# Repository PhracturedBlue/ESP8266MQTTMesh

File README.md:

# ESP8266MQTTMesh
Self-assembling mesh network built around the MQTT protocol for the ESP8266 with OTA support

## NOTE 2020-04
I no longer have resources to work on this, and there are several issues that need to be addressed.  If you have the desire and skill to contribute to this project, please comment on https://github.com/PhracturedBlue/ESP8266MQTTMesh/issues/75 and I will consider your offer of help

## Overview
This code provides a library that can build a mesh network between ESP8266 devices that will allow all nodes to communicate
with an MQTT broker.  At least one node must be able to see a wiFi router, and there must be a host on the WiFi network running
the MQTT broker.
Nodes cannot (generally) communicate between themselves, but instead forward all messages through the broker.
Each node will expose a hidden AP which can be connected to from any other node on the network.  Note:  hiding the AP does not provide
any additional security, but does minimize the clutter of other WiFi clients in the area.

Additionally the library provides an OTA mechanism using the MQTT pathway which can update any/all nodes on the mesh.

This code was developed primarily for the Sonoff line of relays, but should work with any ESP8266 board with sufficient flash memory

Further information about the mesh topology can be found [here](docs/MeshTopology.md)

### Note for version >= 1.0
As of version 1.0 the nodes no longer need to connect to the broker once before use.  Nodes can self-identify other nodes automatically
and do not store any needed state on the broker.  Nodes use the MAC address to identify other nodes, and the ESP8266MQTTMesh code
will change the node's MAC address to match the required pattern.  The MAC addresses are based on both the node's chipID as well as the mesh password, ensuring that each node will have a unique MAC address as well as that multiple meshes can run in the same area independently.

Also, he ESP8266MQTTMesh code no longer uses the SPIFFS file-system.  If you need it, you'll need to initialize it yourself.  If
the mesh is configured to use SSL between nodes, the SSL certs need to be provided during initalization

## OTA
While all nodes must run the same version of the ESP8622MQTTMesh library, each node may run a unique firmware with independent purposes.
The main purpose behind this library was to provide a backbone on which several home-automation sensors could be built.  As such
each node may need different code to achieve its purpose.  Because firmwares are large, and memory is limited on the ESP8266 platform,
there is only a single memory area to hold the incoming firmware.  To ensure that a given firmware is only consumed by the proper nodes,
The firmware defines a unique identifier that distinguishes itself from other code.  A given firmware is broadcast from the MQTT
broker to all nodes, but only nodes with a matching ID will update.

## Using the Library
### Prerequisites
This library has been converted to use Asynchronous communication for imroved reliability.  It requires the following libraries to be installed
* AsyncMqttClient
* ESPAsyncTCP
* Arduino ESP8266 Core version 2.4

PlatformIO is strongly recommended, and installation instructions can be found [here](http://docs.platformio.org/en/latest/platforms/espressif8266.html)).

**NOTE:** Enabling SSL will add ~70kB to the firmware size, and may make it impossible to use OTA updates depending on firmware and flash size.

If OTA support is desired, the esp8266 module must have at least 1M of Flash (configured as >=784k ROM).  The OTA image is stored
between the end of the firmware image and the beginning of the filesystem (i.e. not in the filesystem itself) or the end of flash if
no filesystem is present.  Thus, ithe maximum firmware size is ~ 1/2 the available Flash.

### Library initialization
The ESP8266MQTTMesh only requires 2 parameters to initialize, but there are many additional optional parameters:
```
ESP8266MQTTMesh mesh = ESP8266MQTTMesh::Builder(networks, mqtt_server, mqtt_port).build();
```
- `wifi_conn networks[]` *Required*: A list of SSIDs/BSSIDs/passwords to search for to connect to the wireless network.  The list should be terminated with a NULL element.
- `const char *mqtt_server` *Required*: Host which runs the MQTT broker
- `int mqtt_port` *Optional*: Port which the MQTT broker is running on.  Defaults to 1883 if MQTT SSL is not enabled.  Defaults to 8883 is MQTT SSL is enabled

Additional Parameters can be enabled via the *Builder* for example:
```
ESP8266MQTTMesh mesh = ESP8266MQTTMesh::Builder(networks, mqtt_server, mqtt_port)
                       .setVersion(firmware_ver, firmware_id)
                       .setMeshPassword(password)
                       .build();
```
These additional parameters are specified before calling build(), and as few or as many can be used as neeeded.

```
setVersion(firmware_ver, firmware_id)
```
- `const char *firmware_ver`: This is a string that idenitfies the firmware.  It can be whatever you like.  It will be broadcast to the MQTT broker on successful connection
- `int firmware_id`:  This identifies a specific node codebase.  Each unique firmware should have its own id, and it should not be changed between revisions of the code

```
setMqttAuth(username, password)
```
- `const char *username`: The username used to login to the MQTT broker
- `const char *password`: The password used to login to the MQTT broker

```
setMeshPassword(password)
```
- `const char *password`: The password to use when a node connects to another node on the mesh.  Default: `ESP8266MQTTMesh`

```
setMeshSSID(ssid)
```
- `const char *ssid`: The SSID used by mesh nodes.  All nodes will use the same SSID, though this isn't noticeable due to nodes using hidden networks.  Default: `esp8266_mqtt_mesh

```
setMeshPort(port)
```
- `int port`: Port for mesh nodes to listen on for message parsing. Default: `1884`

```
setTopic(in_topic, out_topic)
```
- `const char *in_topic`: MQTT topic prefix for messages sent to the node.  Default: `esp8266-in/`
- `const char *out_topic`: MQTT topic prefix for messages from the node. Default: `esp8266-out/`

If SSL support is enabled, the following optional parameters are available:
```
setMqttSSL(enable, fingerprint)
```
- `bool enable`: Enable MQTT SSL support.  Default: `false`
- `const uint8_t *fingerprint`: Fingerprint to verify MQTT certificate (prevent man-in-the-middle attacks)

```
setMeshSSL(cert, cert_len, key, key_len, fingerprint)
```
- `const uint8_t *cert`: Certificate
- `uint32_t cert_len`: Certificate length
- `const uint8_t *key`: Certificate key
- `uint32_t key_len`: Certificate key length
- `uint8_t *fingerprint`: Certificate fingerprint (SHA1 of certificate)

### Interacting with the mesh
Besides the constructor, the code must call the `begin()` method during setup.

If messages need to be received by the node, execute the `callback()` function during setup with a function pointer
(prototype: `void callback(const char *topic, const char *payload)`)

To send messages to the MQTT broker, use one of the publish methods:
```
publish(topic, payload, msgCmd)
publish_node(topic, payload, msgCmd)
```
The `publish` function sends messages with the `out_topic` prefix, and will not be relayed to any nodes.  The `publish_nodes`
function will send messages with the `in_topic` prefix and will be relayed back to all nodes

- `const char *topic`: the message topic (will be appended to the topic-prefix)
- `const char *payload`: The message to send (must be less than 1152 bytes in length)
- `enum MSG_TYPE msgCmd`: The MQTT Retail/QoS parameters (optional).  Must be one of: `MSG_TYPE_NONE`,
  `MSG_TYPE_QOS_0`, `MSG_TYPE_QOS_1`, `MSG_TYPE_QOS_2`, `MSG_TYPE_RETAIN_QOS_0`, MSG_TYPE_RETAIN_QOS_1`,
  `MSG_TYPE_RETAIN_QOS_2`.  Default: `MSG_TYPE_NONE`

### SSL support
SSL support is enabled by defining `ASYNC_TCP_SSL_ENABLED=1`.  This must be done globally during build.

Once enabled, SSL can be optionally enabled between the node and the MQTT broker or between mesh nodes (or both).

#### Using SSL with the MQTT Broker
**WARNING:** Make sure you do not use SHA512 certificate signatures on your MQTT broker.  They are not suppoorted by ESP8266 properly
Using an optional fingerprint ensures that the MQTT Broker is the one you expect.  Specifying a fingerprint is useful to prevent man-in-the-middle attacks.
The fingerprint can be generated by running:
```
utils/get_mqtt_fingerprint.py --host <MQTT host> --post <MQTT port>
```
This will also check the signature to make sure it is compatible with ESP8266

#### Using SSL between mesh nodes
**NOTE:** Enabling SSL between mesh nodes should not provide additional security, since the mesh connections are already secured via WPA, so enabling this is not recommended

Generate the certificate, key and fingerprint:
```
utils/gen_server_cert.sh
```

Add the resulting ssl_cert.h to your project.  then add to the Builder `setMeshSSL(ssl_cert, ssl_cert_len, ssl_key, ssl_key_len, ssl_fingerprint)`

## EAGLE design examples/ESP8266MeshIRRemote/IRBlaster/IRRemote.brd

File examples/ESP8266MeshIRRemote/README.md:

# ESP8266MeshIRRemote

This is an example of an IR Blaster controlled via MQTT commands

The blaster uses Pronto codes (though it should be easy to add support for all protocols handled by the IRRemote library).
The Pronto protocol is very flexible, and should be able to handle virtually all IR codes.

Codes can be saved in a file on the device to make it easy to send frequently used codes

## Hardware

The IRBlaster directory contains the Eagle libraries for the IRBlaster used in this example.

The board is quite basic.  It uses an ESP01 module along with a 2n7000 to drive an IR LED.  A LM1117-3.3 module is connected
to a mini-usb to provide power.

This was built before Eagle
was moved to a subscription plan.  I have since moved to using KiCad, but there was no reason to redesign the schematics.

A PDF of the schematic is provided.  Boards can be ordered from OshPark here:
<a href="https://oshpark.com/shared_projects/EaJlztYI"></img></a>

## MQTT Commands

| Topic | Message | Description |
|-------|---------|-------------|
| \<topic>/send            | code=\<pronto code>                                           | send specified code one time |
| \<topic>/send            | repeat=5,code=\<pronto code>                                  | send specified code 5 times |
| \<topic>/send            | repeat=5,code=\<pronto code1>,repeat=3,pronto=\<pronto code2>  | send code1 5 times followed by sending code2 3 times |
| \<topic>/send            | repeat=5,file=\<filename1>,file=\<filename2>,...               | send pronto code previously saved in 'filename1' 5 times, followed by the contents of 'filename2' |
| \<topic>/list            | ""                                                           | returns a list of all saved files |
| \<topic>/debug           | \<1|0>                                                        | enable/disable debugging messages over MQTT |
| \<topic>/save/\<filename> | code=\<pronto code>                                           | save specified pronto code to 'filename' on esp8266 device |
| \<topic>/read/\<filename> | ""                                                           | return contents of 'flename' via MQTT |

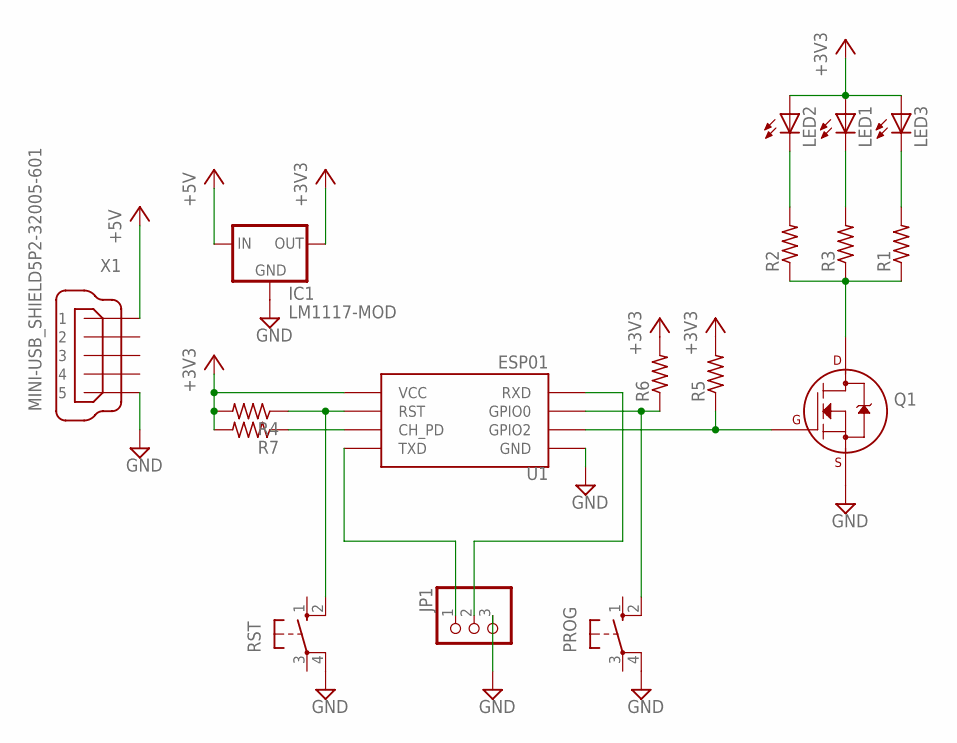
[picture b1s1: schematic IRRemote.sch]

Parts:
IC1: LM1117-MOD; TO220BV
JP1: PINHD-1X3; 1X03
LED1, LED2, LED3: LED5MM
PROG: 10-XX; B3F-10XX
Q1: 2N7000_TO92; TO-92
R1, R2, R3, R4, R5, R6, R7: R-US_0309/10; 0309/10
RST: 10-XX; B3F-10XX
U1: ESP01; ESP01A
X1: MINI-USB_SHIELD5P2-32005-601; 32005-601

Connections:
+3V3: IC1.2 (VOUT), LED1.A, LED2.A, LED3.A, R4.2, R5.2, R6.2, R7.2, U1.VCC
+5V: IC1.3 (VIN), X1.1
GND: IC1.1 (GND), JP1.3, PROG.4 (P1), Q1.1 (S), RST.4 (P1), U1.GND, X1.5
unnamed: Q1.3 (D), R1.1, R2.1, R3.1
unnamed: LED2.K (C), R2.2
unnamed: LED1.K (C), R3.2
unnamed: LED3.K (C), R1.2
unnamed: Q1.2 (G), R5.1, U1.GPIO2
unnamed: R4.1, RST.2 (S1), U1.RST
unnamed: PROG.2 (S1), R6.1, U1.GPIO0
unnamed: R7.1, U1.CH_PD
RX: JP1.2, U1.RX (RXD)
TX: JP1.1, U1.TX (TXD)

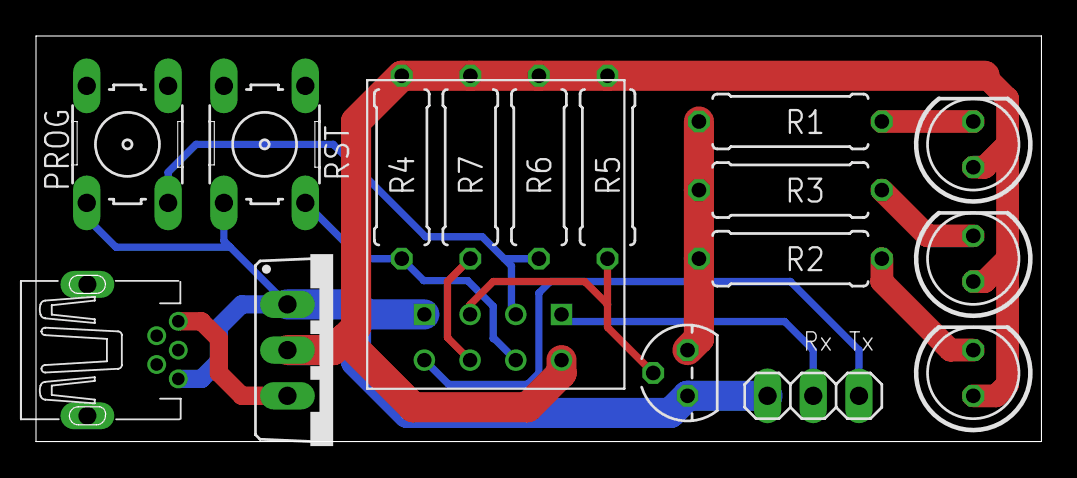
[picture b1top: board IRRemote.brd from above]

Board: 2 copper layers, 55.9 x 22.5 mm, 17 parts (0 on the bottom side), 13 nets.

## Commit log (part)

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2017-04-10 Cleanup file names. Add initial support for message parsing
2017-04-10 Finish adding callback capability. Remove need for static functions
2017-04-10 Add USER_LIBS variable
2017-04-10 Setup publish and callbacks
2017-04-11 Convert to library syntax. Remove Utils
2017-04-11 Moved credentials into example
2017-04-11 Cleanup compile warnings
2017-04-11 Only handle messgaes targeting this node. Fix trivial bugs in Sensor
2017-04-12 Add HLW8012 power sensor support
2017-04-12 Add broadcast message handling
2017-04-12 Add licence
2017-04-12 Separate inputand output topics
2017-04-14 Initial work to move away from String objects
2017-04-14 A bit more String removal
2017-04-14 More String removal
2017-04-14 Remove rest of Strings from library
2017-04-14 Initial OTA update implementation
2017-04-15 Create README.md
    Initial description
2017-04-15 Allow control of debug messages
2017-04-15 Added firmware_id check. Bugfixes
2017-04-15 Add utility to upload OTA. Fix several bugs. Upload now works. Final reboot/flash copy is still broken
2017-04-15 OTA seems to be working now
2017-04-16 Initial import of IRRemote
2017-04-16 Fix sending bssid to broker. rename setup() to begin()
2017-04-16 rewrote IRRemote to use the mesh network
2017-04-16 Further documentation
2017-04-23 Disable HLW8012 interrupts during wifi connection to prevent lockup. Handle connetcion incrementally so as not to stall the main loop
2017-04-23 Add description of ESP8266MeshSensor example
2017-04-23 Create a desciption of the IRBlaster example
2017-04-23 Typo
2017-04-23 Add IRBlaster board
2017-04-23 Update IRBlaster description
2017-06-07 Properly listen on mesh_port. Fix regression in KeyValue parser. Send local messages back to proper IP
2017-06-08 Add basic config.mk options
2017-06-08 Basic Hello World examole
2017-06-08 Use enums rather than integers to make code more readable
2017-06-10 Allow use of alternate LED pin. Only send on connection
2017-06-10 Rewrite WifiClient handling to prevent deadlock. Requires esp8266 library 2.4.0-rc1 or newer
2017-06-12 Disable AP when we lose connection to the MQTT broker. Handle MQTT::publish in the same loop as the mesh publish, rather than immediately. Move back to ESP8266 2.3.0 API (Code will autodetect 2.3.0 o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
2017-06-15 Add timing debug
2017-06-15 Move source into src dir
2017-06-15 Convert MQTT server from PubSubClient to AsyncMqttClient
2017-06-17 Finish initial Async conversion
2017-06-17 Fix prerequisites
2017-06-18 Info on OTA
2017-06-18 Remove mesh loop. Mesh is now fully asynchronous
2017-06-23 Increase logging. try to preserve channel when starting AP
2017-07-09 Add initial upport for SSL
2017-07-09 Rename debug variables to prevent comple warnings
2017-07-11 Mior fixes to get SSL working. Add build script for generating SSL keys. Provide sample keys for demo
2017-07-11 Add fingerprint generator
2017-07-11 Disconnect on bad MQTT fingerprint
2017-07-11 Add documentation about SSL support
2017-07-11 Check for sha512 signatures. Improve docs
2017-07-11 Connvert ESP8266MeshIRRemote to platformio
2017-07-11 Enable platformio for ESP8266MeshSensor
2017-07-11 Minor library.json updates
2017-07-13 Enable MQTT authentication. Switch to a Builder() mechanism for initializing Mesh
2017-07-15 Fix MQTT port handling
2017-07-16 Add bug template
2017-07-16 Remove unnecessary formatting from bug template
2017-07-18 sha384 is also disallowed
2017-07-18 More fingerprint-checker fixes
2017-08-02 Bump version to 0.8.3
2017-08-05 Fix OTA update code. Bump version to 0.8.4
2017-08-07 Rename credentials.h.example to credentials.h
2017-08-07 Updated with more detailed description
2017-11-05 Make HellloWorld example easier to configure
2017-11-05 Bump version to 0.8.5
2017-11-26 Add buildptr() to allow deferred initialization
2017-11-29 Add stack dumptrace utility
2017-11-30 Properly initialize variables when mesh object is created dynaically
2017-12-02 Enable upto 999 nodes
2017-12-02 Enable sending firmware to a single node. enable 'fw/' command to get firmware id from nodes
2017-12-03 Add assertion that proper version of ESP8266 lib is in use
2017-12-03 Enable control of Sonoff switch
2017-12-03 get proper function name
2017-12-03 Use latest ESPAsyncTCP. Bump version
2017-12-03 Update README.md
    Document that development/staging branch of esp8266 is now needed for both SSL and non-SSL compilation
2017-12-03 Show Chip ID of each node
2017-12-03 Alternative check for Arduino-Core 2.4.0. update platform to new method
2017-12-04 Don't override libc strlcat
2017-12-04 Bump version to 0.8.8
2017-12-04 Add support for changing topic and specifiying individual nodes for OTA
2017-12-05 Add Filesystem documentation
2017-12-10 Support hidden WiFi networks
2017-12-14 Update send_ota.py
    added SSL support
    added MQTT authentification
2017-12-14 Update send_ota.py
    deleted unnecessary line
2017-12-14 Update send_ota.py
    changed name of argument from passwd to password
2018-01-05 Implement ability to specify qos and retain flags for published messages. This change is NOT backwards compatible, and requires all nodes to be updated to use the new ESP8266MQTT library
2018-01-14 Fix bug with msgType being sent to children
2018-01-14 try to fix MsgType again
2018-02-28 Major rewrite to remove dependncy on pr-connect to broker. Not backwards compatible
2018-02-28 Add publish_node function. ase mesh_bssid_key on mesh_password. Rework LFSR
2018-03-04 Remove all use of SPIFFS ((SSL Certs are now compiled in). Fix MAC generation. Fix ssid detection.
2018-03-04 Fix fingerprint checking during SSL connection
2018-03-04 Minor documentation cleanup
2018-03-04 Update HelloWorld docs
2018-03-04 Add initial topology documentation
2018-03-04 Fix image linking
2018-03-04 No longer relevant for 1.0
2018-03-04 Add link to additional documentation
2018-03-04 Improve OTA reliability. Wait for node-response before continuing rather than relying on timeout
2018-03-04 Bump revision to 1.0.2
2018-03-04 Add ESP32 target and compile clean
2018-03-05 Need to save WifiEventHandler's to prevent auto-deletion
2018-03-06 add file library.properties to work with arduino IDE
2018-03-06 Backport library properties to 1.0.2
2018-03-09 Bump version to 1.0.3
2018-03-27 Fix network sorting (As per #44)
2018-03-27 Bump version to 1.0.4
2018-03-30 Hotfix for update By Software ID
2018-03-31 Try to make OTA more robust
2018-12-24 Added Support for controlling OTA Package Length
    Since the ESP can only handle a specific maximal length of Packages, and this Length is dependent on different Factors like Libary Versions and build Parameters, I have added an option to controll th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
2018-12-26 more reliable Connection to AP
    if the Node scans the Networks and finds an Acess Point with a bad connection it now prefers to connect to a nother Node instead of to the AP.
2018-12-28 Added basic Node Functions
    Added Functions like the ability to ping an node and receive an Answer back (to know if it is still there) and an Restard for the Nodes.
    if using an custom Smarthome System, you can set the Ping to 0, and the node will turn it back to 1, exept it is offline, so you can create an Indicator if the Node is online.
2018-12-29 reasigned Function declaration
2018-12-29 fixed little Mistake
2018-12-29 Fixing little Mistake
2018-12-29 once more...
2018-12-29 finaly done right
2018-12-29 added ESP.restart() to die Macro
2018-12-29 added some Messages to the buildin Functions
2018-12-29 sending Ping Answer on InTopic exept on out Topic
2018-12-29 sending on in topic was a verry bad Idea, resetting to last commit
2019-01-20 not always favour Acess Point
    in the Network Sorting Routine now an real Acess Point is not always favourited above the Mesh Network, only if the AP connection is solid, else take best Connection no regards if it is over the Mesh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
2019-01-26 fixed wrong Signal Sorting
    now the Signals are sorted by RSSI, and if Signal is from AP or Mesh only is important, if AP Signal is quite decent, else take just the Strongest Signal.
2019-01-26 sorted the Wrong Way, now fixing it
2019-03-19 connect to Access Point only if the singal is at least okay or there is no mesh node with a better signal
2019-07-26 removed String Terminator in base64_decode
    String Terminator was a verry bad Idea, because it causes an Overflow in decoding the MD5 Sum and writing String Terminators in the executed Flash by an OTA Update
    see #67
2019-07-26 verry little Tweeks with large Impact, for example prevent a Buffer Overflow, which happened on every OTA Update and little changes to make the Code mor readable
2019-07-27 Reboot delay to propagate flash command to mesh network
2019-07-27 Change topic to 'IoT'
2019-07-27 Change get_fw_string
2019-07-27 Prevent crash when onWifiDisconnect is called 2 times (eg. wrong password)
2019-07-27 Update erase_sector to prevent disconnect mesh clients
2019-07-27 Connect message from mesh nodes
2019-07-27 Remove warnings
2019-07-27 Join partial MQTT message
2019-07-27 dbgPrint change extra
2019-07-27 mannually merged JaroSu's changes
2019-07-27 Show MAC of connected node
2019-07-27 Add nodeType ID Uppercase
2019-07-27 reset in and out Topics
2019-07-27 readded the Option to configure Package Size in sendOTA
2019-09-03 added sending reset Reason on mqtt connect
2019-09-03 set Debuging all as default
2019-09-03 publishes some Information on first Connect
2019-09-07 fixed ResetReason on no restart
2019-09-07 fixed little stupid Error
2019-09-07 restart Reason was wrong Way around.
2019-12-27 failproving onMqttMessage Function for wrong msg Lengths
2019-12-27 made reconnect Routina more robust and tidied up a bit
2019-12-28 removed unused Variables and wrote a few comments
2019-12-28 now always deletes Main Connection object on disconnect!
2019-12-28 fixed Syntax Error with removing WIFI_CONN
2019-12-28 Syntax Error Fixing
2019-12-28 silly debugging
2019-12-28 removed deletion of Main Acess Point Reference
2020-01-06 values Mesh Network now a bit more then the direct Acess point if the AP has a bad connection
2020-02-16 sending only one message per package instead of 4
2020-02-16 send.ota for Module ID's with capital Letters
2020-02-16 removed esp32 Support
2020-02-17 finaly working again
2020-02-17 optical Stuff
2020-02-17 missed String Terminator at End of String
2020-02-17 more Messages
2020-02-17 little Fixes
2020-02-17 chanched Package end Character from String Terminator to new Line
2020-02-17 little Fix
2020-02-18 added some Delays between connection Messages
2020-02-29 made connected() Function more stable if connected over the Mesh
2020-02-29 fixed problem with member and Static Function
2020-04-15 Note about help needed
2020-05-24 properly close connection if to manny connections to AP
2020-05-27 corrected
2023-01-06 Fixed missing include
2023-02-05 fixed bug in include
    ESP32Ticker.h is now called Ticker.h
    # Conflicts:
    # src/ESP8266MQTTMesh.h
2023-02-05 added method setID
    useful if the default ID is in conflict with pre-existing devices
    # Conflicts:
    # src/ESP8266MQTTMesh.cpp
2023-02-05 Fixed some compile issue for ESP32
2023-02-11 Increased timeout to improve stability
    added also a proper error raising
2023-06-08 Corrected bug related to newer ESP8266 board firmware version
2023-07-23 Removed some delays
    delays were causing instabilities
    furthermore the MQTT should care for the queue
    so delays are not needed
2024-01-05 Implemented blinking of led due to connection status
    does not seem to work
2024-01-06 Implemented topic to get availability of node
2024-01-29 library.json reverted to PhracturedBlue repo version
2024-09-07 fixed wifi event type
    type names in ESP32 is changed in new version from system to arduino
2024-09-07 Fixed new type issue with new ESP32 library
2024-09-07 added ifdef to use code fix only for ESP32
    TODO check if new version of ESP8266 is compatible with this fix or not
2024-09-08 Added missing include
2024-09-08 changed type names to be compatible with ESP32 3.0.4
2024-09-08 changed event names in agreement with ESP32 3.0.4
2025-02-22 implemented method to set the status pin
